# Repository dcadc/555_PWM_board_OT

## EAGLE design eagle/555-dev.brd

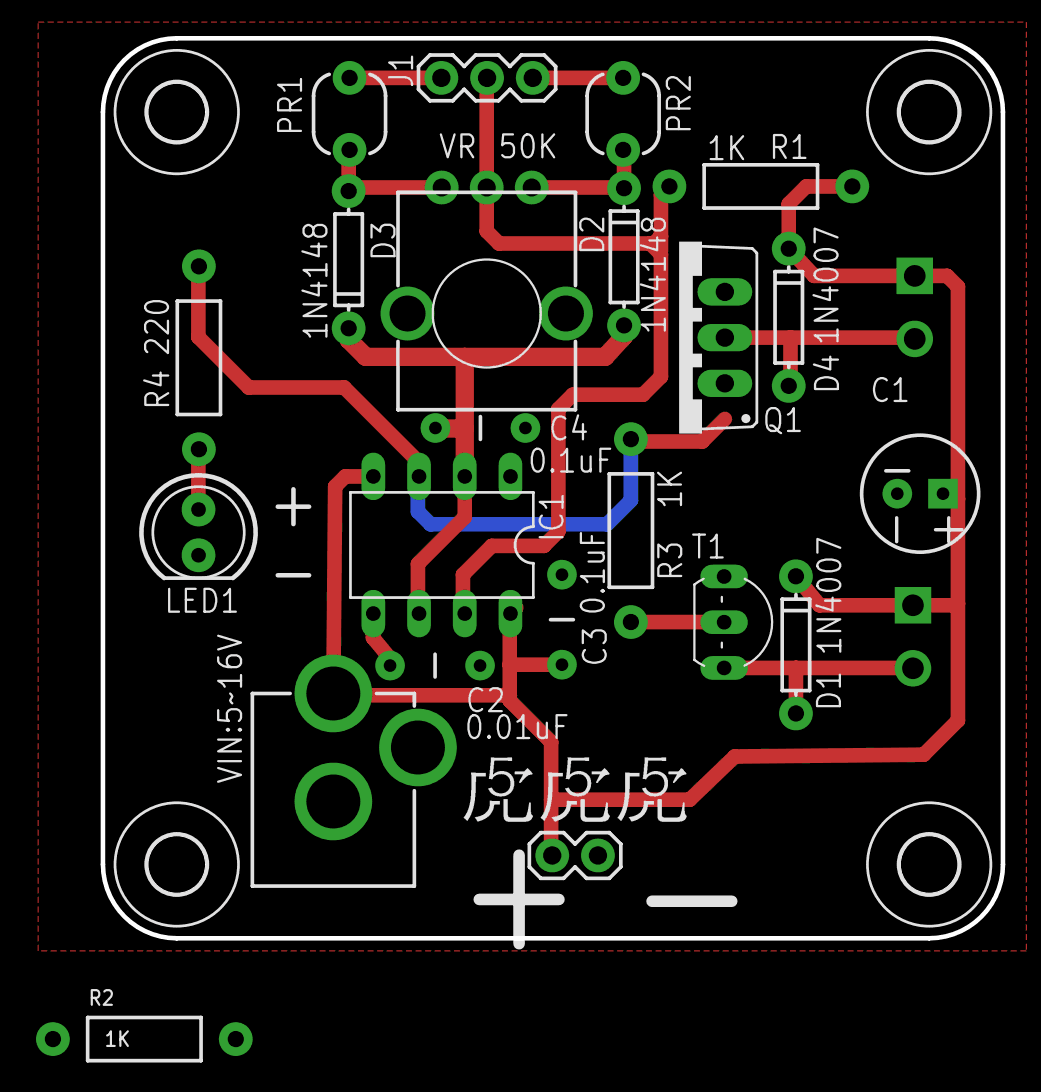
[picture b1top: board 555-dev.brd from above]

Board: 2 copper layers, 50.0 x 50.0 mm, 29 parts (0 on the bottom side), 15 nets.

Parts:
C1: 100uF; CPOL-RADIAL-100UF-25V
C2: 0.01uF; CAP-PTH-5MM
C3, C4: 0.1uF; CAP-PTH-5MM
D1, D4: 1N4007; DIODE-1N4148-KIT
D2, D3: 1N4148; DIODE-1N4148
H5, H6, H7, H8: MOUNT-HOLE3.2; 3,2
IC1: NE555; DIL08
J1: 1X03
J3-1: 1X02
JP1, JP2: SCREWTERMINAL-3.5MM-2-NS
JP3: POWER_JACKPTH; POWER_JACK_PTH
LED1: LED5MM-KIT
PR1, PR2: PHOTOCELLPTH-KIT; PHOTOCELL-KIT
Q1: IRF740/TIP120; TO220BV
R1, R2, R3: 1K; AXIAL-0.4
R4: 220; AXIAL-0.4
T1: 2N2222; TO92-EBC-OVAL
U$1: LOGO
VR: 50K; ALPS_POT_KIT

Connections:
555_DISCH: IC1.7, J1.2, R1.P$1, VR.P$2
555_TRIG: C4.1, D2.A, D3.C, IC1.2, IC1.6
GND: C1.2, C2.2, C3.1, C4.2, IC1.1, J3-1.1, JP3.GND, LED1.K, Q1.S, T1.E
LOAD1-: D1.A, JP1.2, T1.C
LOAD2-: D4.A, JP2.2, Q1.D
unnamed: Q1.G, R2.P$1
unnamed: D2.C, PR2.1, VR.P$1
unnamed: D3.A, PR1.1, VR.P$3
unnamed: C2.1, IC1.5
unnamed: R3.P$1, T1.B
unnamed: LED1.A, R4.P$1
OUT: IC1.3, R2.P$2, R3.P$2, R4.P$2
PR1: J1.1, PR1.2
PR2: J1.3, PR2.2
VCC: C1.1, C3.2, D1.C, D4.C, IC1.4, IC1.8, J3-1.2, JP1.1, JP2.1, JP3.PWR, R1.P$2

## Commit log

2016-03-27 :circus_tent: Added .gitattributes
2016-03-27 upload sch
2016-03-27 beta
2016-03-27 add photoresistor jumper
    select from normal resistor to photoresistor
2016-03-29 add one more photoresistor and change the R network
    user can use the PINS and VR(max/min) to stable the high pulse or the
    low one
    while the frequency is modulated by photoresistors, duty cycle changes
    due to the static pulse width
    simulation: http://goo.gl/erNx82
    Layout to be done
2016-03-30 ver 1
2016-03-31 added LOGO
2016-04-25 change 1N4001 to 1N4148
2016-04-25 change CAP
2016-04-28 add R2 base resistor and change Q1 into TIP120/IRF740
2016-04-28 added base R

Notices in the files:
parts and their libraries:
SparkFun-Passives: Licensing: Creative Commons ShareAlike 4.0 International - https://creativecommons.org/licenses/by-sa/4.0
